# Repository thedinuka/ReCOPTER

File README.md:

# ReCOPTER
Source files for the ReCOPTER paper published in ACRA 2015

If you make use of the material here, please cite the following paper, a copy of which is provided here.
Dinuka Abeywardena, Paul Pounds, David Hunt, and Gamini Dissanayake. Design and Development of ReCOPTER: An Open source ROS-based Multi-rotor Platform for Research. Australasian Conference on Robotics and Automation (ACRA) 2015.

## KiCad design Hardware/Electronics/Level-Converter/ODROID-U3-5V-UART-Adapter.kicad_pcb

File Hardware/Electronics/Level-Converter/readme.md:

Schematics and board files for the level converter board used to communicated between the Pixhawk and the Odroid U3.

The schematics and boad files were prepared using the open source electronics design automation suite KiCad. KiCad is available for download at http://kicad-pcb.org/

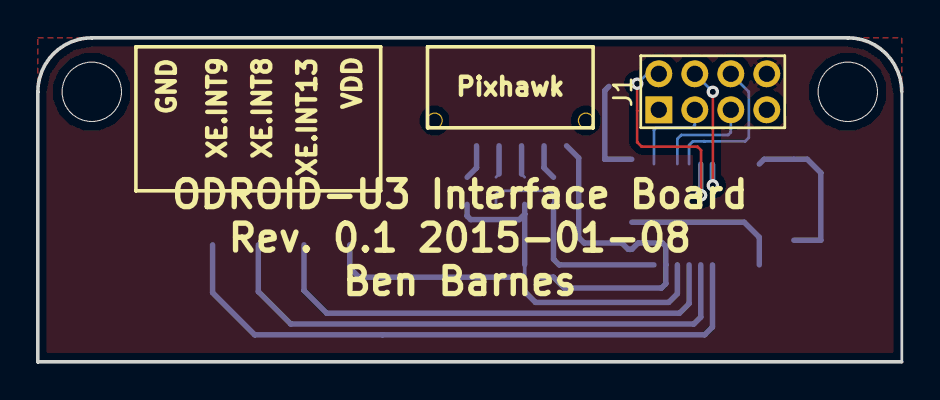
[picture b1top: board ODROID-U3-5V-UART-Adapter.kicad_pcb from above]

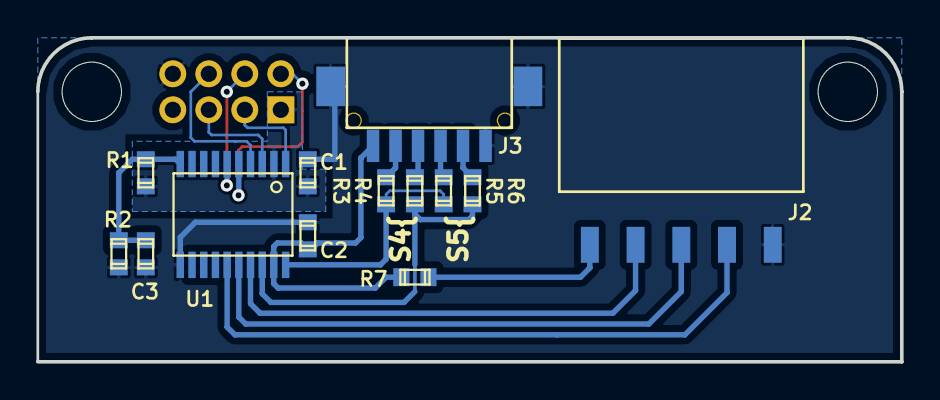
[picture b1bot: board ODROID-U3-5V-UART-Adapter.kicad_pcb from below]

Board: 2 copper layers, 48.0 x 18.0 mm, 16 parts (13 on the bottom side), 19 nets.

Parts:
C1, C2: 10n; c_0603
C3: 1n; c_0603
J1: PIN_HEADER_2X4_2MM_TH; PIN_ARRAY_2MM_4x2
J2: BG300-05-A-L-A
J3: DF13-6P-1.25H
M1, M2: M3_DRILL
R1: 1k; c_0603
R2: 100k; c_0603
R3, R4, R5, R6, R7: 0R; c_0603
U1: TXS0108EPWR; tssop-20

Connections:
+1.8V: C1.1, J1.1, R1.1, U1.2
/PIXHAWK_S4_RX: J3.3, R4.2
/PIXHAWK_S4_TX: J3.2, R3.2
/PIXHAWK_S5_RX: J3.5, R6.2
/PIXHAWK_S5_TX: J3.4, R5.2
/VDD_CONN: J2.1, R7.2
GND: C1.2, C2.2, C3.2, J1.8, J2.5, J3.6, J3.7, J3.8, R2.1, U1.11
GPIO1: J2.2, U1.17
GPIO2: J2.3, U1.16
GPIO3: J2.4, U1.15
OE: C3.1, R1.2, R2.2, U1.10
PIXHAWK_RX: R4.1, R6.1, U1.18
PIXHAWK_TX: R3.1, R5.1, U1.20
UART_0.RXD: J1.3, U1.1
UART_0.TXD: J1.5, U1.3
VDD: C2.1, J3.1, R7.1, U1.19
XE.INT8: J1.2, U1.5
XE.INT9: J1.4, U1.6
XE.INT13: J1.6, U1.4

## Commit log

2015-11-03 Added level converter design files.
2015-11-06 Added frame design
    Added version 1 of the frame design.
2015-11-06 Removed temp files
2015-11-06 changed name from roscopter
2015-11-06 added ACRA paper
2015-11-12 removing old solidworks files
2015-11-12 Added up to date solidworks and autocad models for the frame and required components
2015-11-26 adding the parts list files
2015-11-26 adding information about KiCad
2015-12-15 adding ACRA 2015 presentation and paper
